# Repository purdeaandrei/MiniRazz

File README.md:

# MiniRazz - open hardware controller replacement for the Mini M keyboard.

This is a replacement keyboard controller, for the Unicomp Mini M
keyboard, this is an independent community project that is not endorsed by
Unicomp, and it is not related to any official controller sold by them.

Licensed under CERN-OHL-P v2 or later

## Images

## How to order from JLCPCB:
1. Go to http://jlcpcb.com , sign in to your account (create one if you don't have one)
2. Click Order Now, click Add gerber file
3. Upload the .zip file from the "order" subfolder.
4. Wait for the gerbers to be processed.
5. Check that it correctly detected 4-layerboard.
6. Select PCB Qty you wish to build
7. Specify Layer Sequence, click Yes, And select L1=F_Cu L2=In1_Cu L3=In2_Cu L4=B_Cu
8. Set "Remove Order Number" to "Specify a location"
9. Scroll down, turn on the "SMT Assembly" option, turn it on
10. Select "PCBA Type" = "Economic"
11. Select "Assembly Side" = "Top Side"
12. Select "Tooling holes" = "Added by Customer"
13. Click "I agree to the Terms and Conditions..."
14. Click "Next" on the right side
15. Click "Next" on the right side
16. Click "Add BOM File", upload the "*_bom_jlc.csv" file from the "order" subfolder.
17. Click "Add CPL File", upload the "*_cpl_jlc.csv" file from the "order" subfolder.
18. Click "Process BPM & CPL"
19. Take a look at what parts are available. At the time of writing J2/J3 triomate connectors were only available if pre-ordered (at a higher cost than ordering from DigiKey).
    You may be able to optimize cost by choosing to solder certain parts yourself, through-hole parts being the most likely candidate. (Please see the following section)
20. Click "Next", you will also have to click "Do Not Place" if some components are missing.
21. Check the rotation of components. JLCPCB may change default rotation in their component libraries at any time, and also position and rotation of the triomates has not been verified.
    - Check that component pins line up correctly with pads
    - Check that components which have polarity (usually marked with a dot) are oriented towards an assimetric marking on the silkscreen (for example for the memory and the io expander there's an extra line, while for the RP2040 there's a missing corner line to mark pin 1)
22. Click "Next"
23. Select Product Description: Office Appliance.../Keyboard...
24. Save to Cart, Check Out.

Cost analysis at the time of writing (2024 Aug 11):

| Qty | JLCPCB (USD) | JLC shipping est. (USD) | Digikey Triomates (USD) | Digikey shipping est. (USD) | VAT (19%) USD | Total (USD) | Coast per Board (USD) |
|-----|--------------|-------------------------|-------------------------|-----------------------------|---------------|-------------|-----------------------|
| 5   |   84.34      | 23.80                   | 14.66                   | 30                          | 29.03         | 181.83      | 36.37                 |
| 10  |  106.13      | 29.80                   | 29.32                   | 30                          | 37.10         | 232.35      | 23.24                 |
| 15  |  130.10      | 55.54                   | 43.76                   | 30                          | 49.29         | 308.69      | 20.58                 |
| 20  |  154.18      | 57.74                   | 58.35                   | 30                          | 57.05         | 357.32      | 17.87                 |

## Components of this design that may have to be ordered separately:
- 2 pcs of 16-pin 90-degree triomate connectors / board:
   - Part number: `6-520314-6` (TE Connectivity AMP Connectors)
   - [Digikey](https://www.digikey.com/en/products/detail/te-connectivity-amp-connectors/6-520314-6/1153749)
   - If the 90-degree connectors are not in stock, then you may also be able to get away with vertical ones (part number `6-520315-6`)
      - This has not yet been tested for fit in the keyboard.
   - JLCPCB now has it in its library, however it's not in stock.
     - You can pre-order it, and then have them assemble it, however it may not make financial sense (current costs are higher than from digikey, and you have to order 5 pcs extra for attrition.)
       - If you decide to have JLCPCB assemble this component, it is present in the bom/cpl files, but make sure the connector position/rotations are connect. I could not verify because they weren't in stock at the time I last checked.

## Other through hole components that may make sense to buy separately and to solder yourself:
- USB connector with locking tab
   - Part number: `LUSBA11100` (AMPHENOL COMMUNICATIONS SOLUTIONS)
   - [Digikey](https://www.digikey.com/en/products/detail/amphenol-cs-commercial-products/LUSBA11100/1956311?s=N4IgTCBcDaIDIFUDKAhAggRiwBmyAugL5A)
   - [Farnell](https://ro.farnell.com/amphenol-icc-commercial-products/lusba11100/usb-conn-2-0-type-a-receptacle/dp/2708971?CMP=e-email-sys-orderack-GLB)
- Optional 90 degree headers for solenoid support. You can use one of two options:
   - An 1x4 90-degree header: (recommended)
      - You will need to use single jumper wires to connect the solenoid driver, (or need to crimp a custom cable with dupont connectors)
   - A 2x3 90-degree header: (not recommended)
      - This may not fit well in the space available, and you may need to add tape to isolate the bottom of the backplate.

## Firmware

VIAL-QMK and ZMK firmwares are available, (plain QMK upstreaming will also be attempted).

### VIAL Firmware
Download from here:
https://github.com/purdeaandrei/vial-qmk-minirazz/releases

Use `unicomp_mini_m_minirazz_vial.uf2` or `unicomp_mini_m_minirazz_vial_debug.uf2`

### ZMK Firmware
The ZMK firmware can be downloaded by clicking Releases here: https://github.com/purdeaandrei/minirazz-zmk-config
The keymap can be customized by forking this repository, and editing the keymap. The firmware will be automatically rebuilt by github, and will be available on the "Actions" tab.
If you want to keep your keymap secret, you can copy the content of this repository into a private github repository.

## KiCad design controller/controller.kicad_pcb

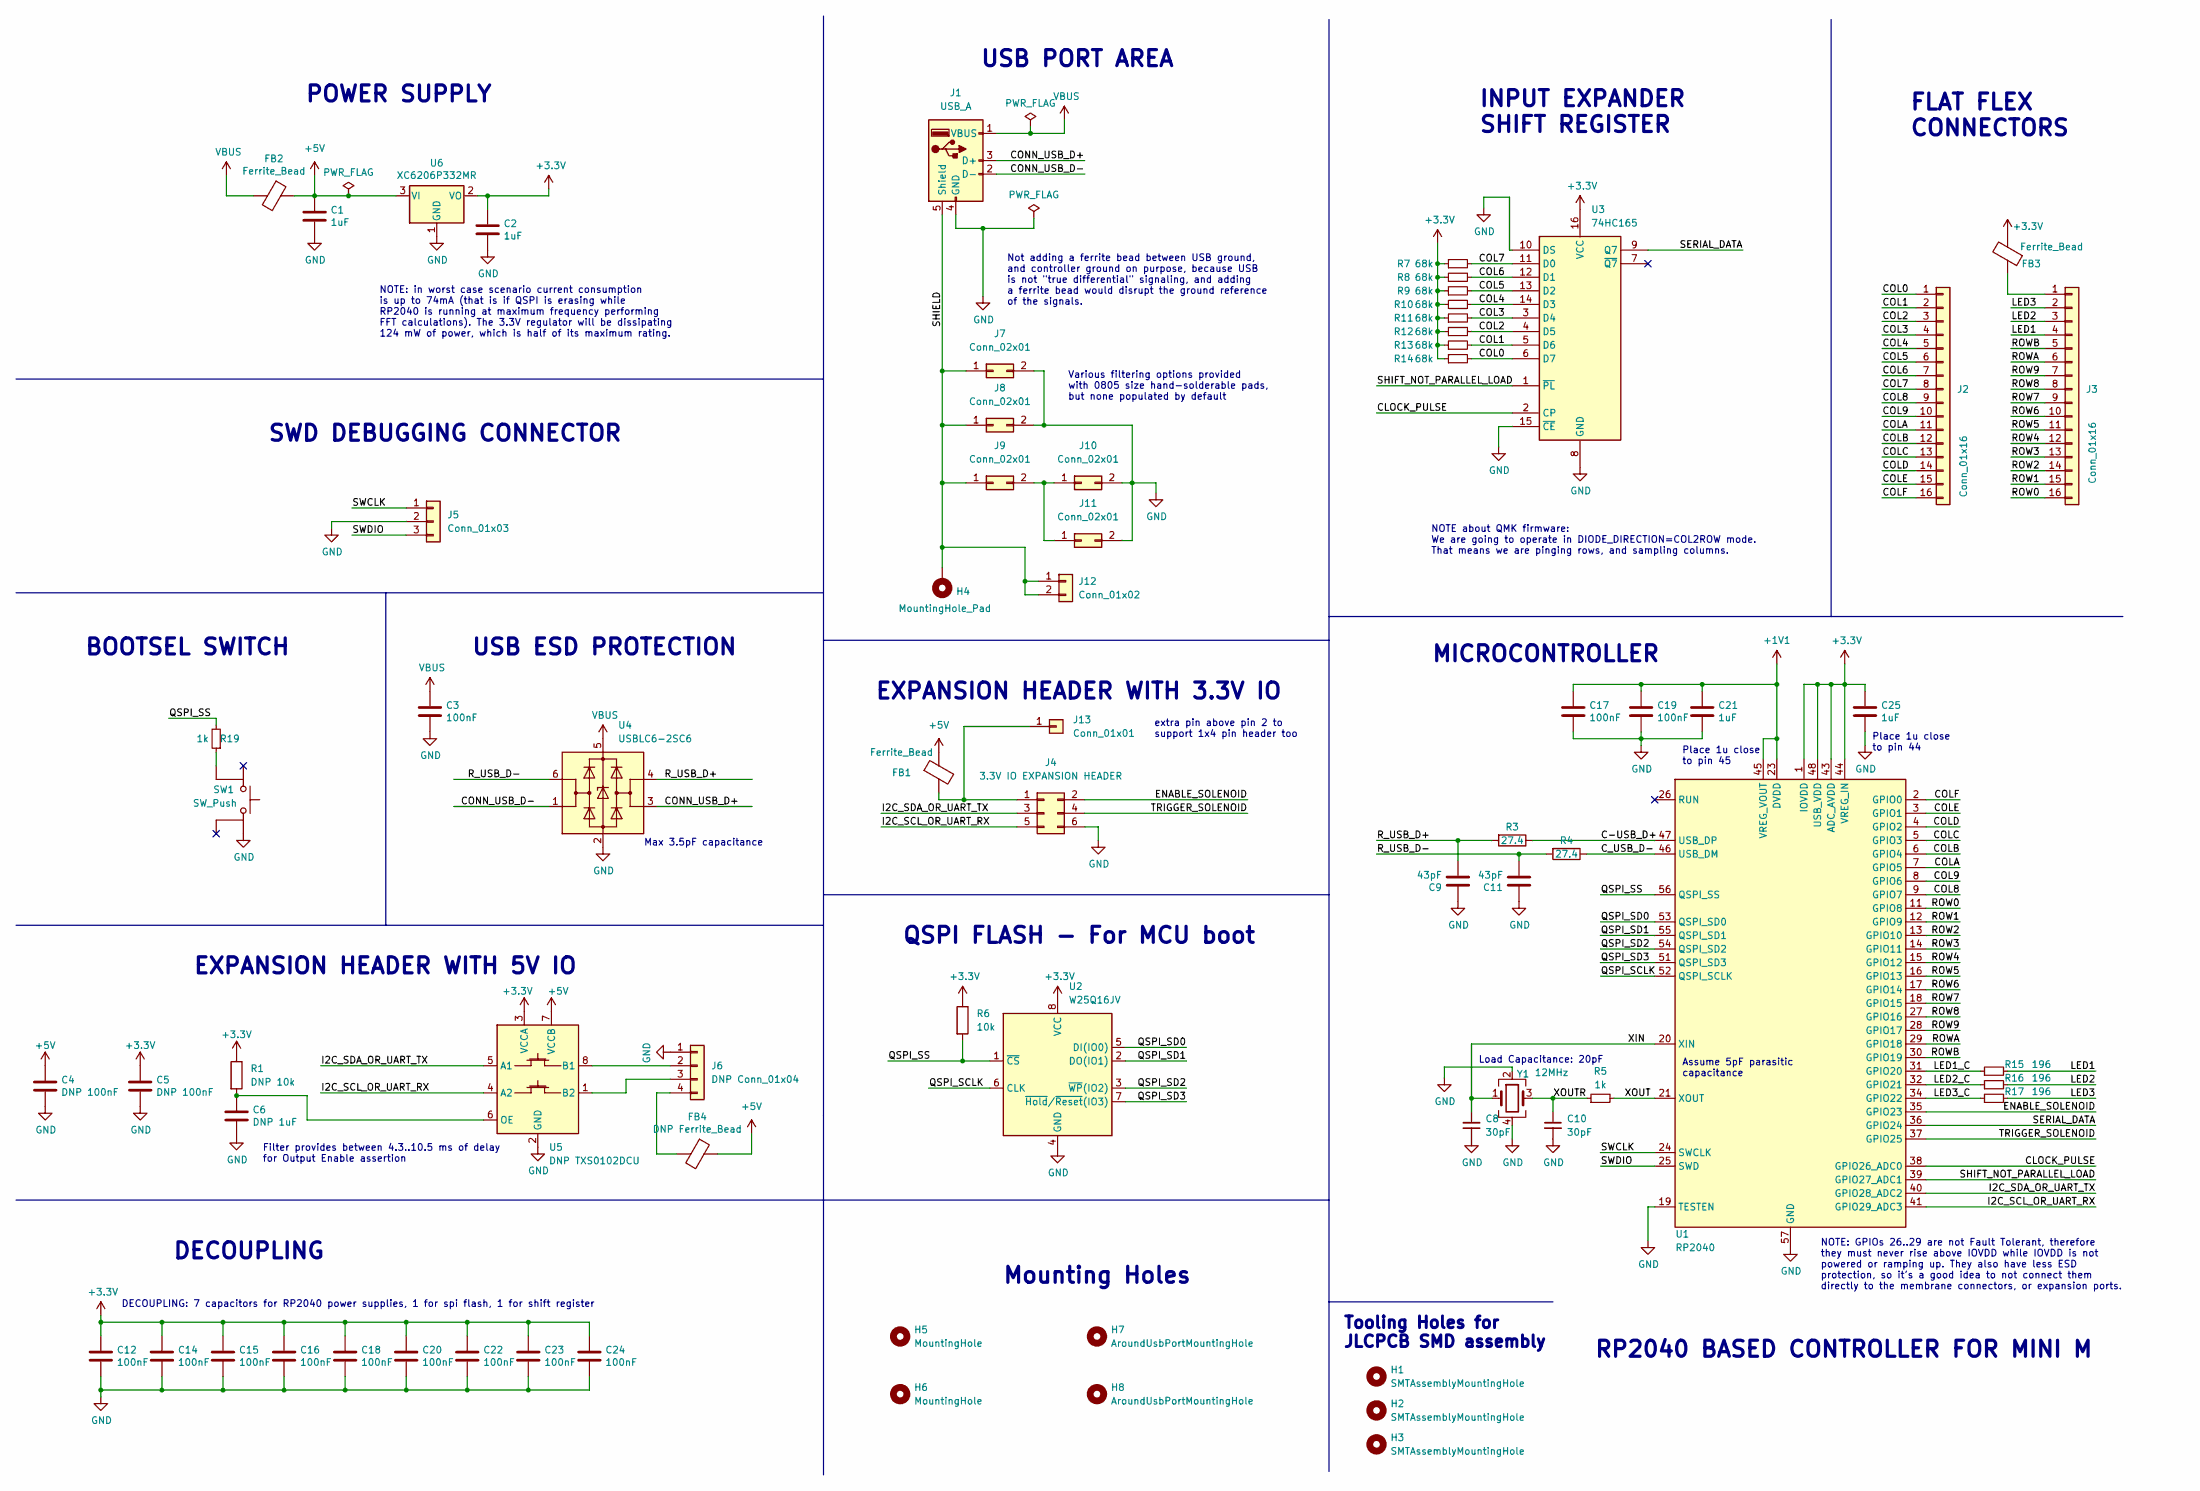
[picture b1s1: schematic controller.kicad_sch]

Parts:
C1, C2, C21, C25: 1uF; C_0402_1005Metric; LCSC C52923
C3, C12, C14, C15, C16, C17, C18, C19, C20, C22, C23, C24: 100nF; C_0402_1005Metric; LCSC C1525
C4, C5: DNP 100nF; C_0805_2012Metric_Pad1.18x1.45mm_HandSolder
C6: DNP 1uF; C_0805_2012Metric_Pad1.18x1.45mm_HandSolder
C8, C10: 30pF; C_0402_1005Metric; LCSC C1570
C9, C11: 43pF; C_0402_1005Metric; LCSC C415393
FB1, FB2, FB3: Ferrite_Bead; L_0805_2012Metric_Pad1.15x1.40mm_HandSolder; LCSC C1015
FB4: DNP Ferrite_Bead; L_0805_2012Metric_Pad1.15x1.40mm_HandSolder; LCSC C1015
H1, H2, H3: SMTAssemblyMountingHole; tooling_hole
H4: MountingHole_Pad; MountingHole_3mm_Pad
H5, H6: MountingHole; MountingHole_3mm
H7, H8: AroundUsbPortMountingHole; MountingHole_3.5mm
J1: USB_A; LUSB_A111_00
J2, J3: Conn_01x16; TE_connectivity_AMP_6-520314-6
J4: 3.3V IO EXPANSION HEADER; PinHeader_2x03_P2.54mm_Vertical_3dhorizontal
J5: Conn_01x03; PinHeader_1x03_P2.54mm_Vertical
J6: DNP Conn_01x04; JST_PH_S4B-PH-K_1x04_P2.00mm_Horizontal
J7, J8, J11: Conn_02x01; C_0805_2012Metric_Pad1.18x1.45mm_HandSolder
J9: Conn_02x01; R_0805_2012Metric_Pad1.20x1.40mm_HandSolder
J10: Conn_02x01; C_0402_1005Metric_Pad0.74x0.62mm_HandSolder
J12: Conn_01x02; JST_PH_B2B-PH-K_1x02_P2.00mm_Vertical
J13: Conn_01x01; PinHeader_1x01_P2.54mm_Vertical_3dhorizontal
R1: DNP 10k; R_0805_2012Metric_Pad1.20x1.40mm_HandSolder; LCSC C25744
R3, R4: 27.4; R_0402_1005Metric; LCSC C284479
R5, R19: 1k; R_0402_1005Metric; LCSC C11702
R6: 10k; R_0402_1005Metric; LCSC C25744
R7, R8, R9, R10, R11, R12, R13, R14: 68k; R_0402_1005Metric; LCSC C36871
R15, R16, R17: 196; R_0402_1005Metric; LCSC C270631
SW1: SW_Push; switch_K2-1187SQ-A4SW-06; LCSC C92584
U1: RP2040; QFN-56-1EP_7x7mm_P0.4mm_EP3.2x3.2mm; LCSC C2040
U2: W25Q16JV; SOIC-8_5.275x5.275mm_P1.27mm; LCSC C82317
U3: 74HC165; SOIC-16_3.9x9.9mm_P1.27mm; LCSC C5613
U4: USBLC6-2SC6; SOT-23-6; LCSC C2827654
U5: DNP TXS0102DCU; VSSOP-8_2.3x2mm_P0.5mm
U6: XC6206P332MR; SOT-23; LCSC C5446
Y1: 12MHz; Crystal_SMD_3225-4Pin_3.2x2.5mm_HandSoldering; LCSC C9002

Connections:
+1V1: C17.1, C19.1, C21.1, U1.23 (DVDD), U1.45 (VREG_VOUT), U1.50 (DVDD)
+3.3V: C2.1, C5.1, C12.1, C14.1, C15.1, C16.1, C18.1, C20.1, C22.1, C23.1, C24.1, C25.1, FB3.2, R1.1, R6.1, R7.1, R8.1, R9.1, R10.1, R11.1, R12.1, R13.1, R14.1, U1.1 (IOVDD), U1.10 (IOVDD), U1.22 (IOVDD), U1.33 (IOVDD), U1.42 (IOVDD), U1.43 (ADC_AVDD), U1.44 (VREG_IN), U1.48 (USB_VDD), U1.49 (IOVDD), U2.8 (VCC), U3.16 (VCC), U5.3 (VCCA), U6.2 (VO)
/C-USB_D+: R3.1, U1.47 (USB_DP)
/CLOCK_PULSE: U1.38 (GPIO26_ADC0), U3.2 (CP)
/COL0: J2.1, R14.2, U3.6 (D7)
/COL1: J2.2, R13.2, U3.5 (D6)
/COL2: J2.3, R12.2, U3.4 (D5)
/COL3: J2.4, R11.2, U3.3 (D4)
/COL4: J2.5, R10.2, U3.14 (D3)
/COL5: J2.6, R9.2, U3.13 (D2)
/COL6: J2.7, R8.2, U3.12 (D1)
/COL7: J2.8, R7.2, U3.11 (D0)
/COL8: J2.9, U1.9 (GPIO7)
/COL9: J2.10, U1.8 (GPIO6)
/COLA: J2.11, U1.7 (GPIO5)
/COLB: J2.12, U1.6 (GPIO4)
/COLC: J2.13, U1.5 (GPIO3)
/COLD: J2.14, U1.4 (GPIO2)
/COLE: J2.15, U1.3 (GPIO1)
/COLF: J2.16, U1.2 (GPIO0)
/CONN_USB_D+: J1.3 (D+), U4.3 (I/O2)
/CONN_USB_D-: J1.2 (D-), U4.1 (I/O1)
/C_USB_D-: R4.1, U1.46 (USB_DM)
/ENABLE_SOLENOID: J4.2, U1.35 (GPIO23)
/I2C_SCL_OR_UART_RX: J4.5, U1.41 (GPIO29_ADC3), U5.4 (A2)
/I2C_SDA_OR_UART_TX: J4.3, U1.40 (GPIO28_ADC2), U5.5 (A1)
/LED1: J3.4, R15.2
/LED1_C: R15.1, U1.31 (GPIO20)
/LED2: J3.3, R16.2
/LED2_C: R16.1, U1.32 (GPIO21)
/LED3: J3.2, R17.2
/LED3_C: R17.1, U1.34 (GPIO22)
/QSPI_SCLK: U1.52 (QSPI_SCLK), U2.6 (CLK)
/QSPI_SD0: U1.53 (QSPI_SD0), U2.5 (DI(IO0))
/QSPI_SD1: U1.55 (QSPI_SD1), U2.2 (DO(IO1))
/QSPI_SD2: U1.54 (QSPI_SD2), U2.3 (~WP(IO2))
/QSPI_SD3: U1.51 (QSPI_SD3), U2.7 (~Hold/~Reset(IO3))
/QSPI_SS: R6.2, R19.2, U1.56 (QSPI_SS), U2.1 (~CS)
/ROW0: J3.16, U1.11 (GPIO8)
/ROW1: J3.15, U1.12 (GPIO9)
/ROW2: J3.14, U1.13 (GPIO10)
/ROW3: J3.13, U1.14 (GPIO11)
/ROW4: J3.12, U1.15 (GPIO12)
/ROW5: J3.11, U1.16 (GPIO13)
/ROW6: J3.10, U1.17 (GPIO14)
/ROW7: J3.9, U1.18 (GPIO15)
/ROW8: J3.8, U1.27 (GPIO16)
/ROW9: J3.7, U1.28 (GPIO17)
/ROWA: J3.6, U1.29 (GPIO18)
/ROWB: J3.5, U1.30 (GPIO19)
/R_USB_D+: C9.2, R3.2, U4.4 (I/O2)
/R_USB_D-: C11.2, R4.2, U4.6 (I/O1)
/SERIAL_DATA: U1.36 (GPIO24), U3.9 (Q7)
/SHIELD: H4.1, J1.5 (Shield), J7.1, J8.1, J9.1, J12.1, J12.2
/SHIFT_NOT_PARALLEL_LOAD: U1.39 (GPIO27_ADC1), U3.1 (~PL)
/SWCLK: J5.1, U1.24 (SWCLK)
/SWDIO: J5.3, U1.25 (SWD)
/TRIGGER_SOLENOID: J4.4, U1.37 (GPIO25)
/XIN: C8.1, U1.20 (XIN), Y1.1
/XOUT: R5.2, U1.21 (XOUT)
/XOUTR: C10.1, R5.1, Y1.3
unnamed: C6.1, R1.2, U5.6 (OE)
unnamed: FB1.2, J4.1, J13.1
unnamed: FB3.1, J3.1
unnamed: FB4.2, J6.4
unnamed: J6.2, U5.8 (B1)
unnamed: J6.3, U5.1 (B2)
unnamed: J9.2, J10.1, J11.1
unnamed: R19.1, SW1.2

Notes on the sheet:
DECOUPLING: 7 capacitors for RP2040 power supplies, 1 for spi flash, 1 for shift register
USB PORT AREA
Tooling Holes for JLCPCB SMD assembly
Place 1u close to pin 45
Max 3.5pF capacitance
Place 1u close to pin 44
FLAT FLEX CONNECTORS
Not adding a ferrite bead between USB ground, and controller ground on purpose, because USB is not "true differential" signaling, and adding a ferrite bead would disrupt the ground reference of the signals.
Various filtering options provided with 0805 size hand-solderable pads, but none populated by default
EXPANSION HEADER WITH 5V IO
NOTE: GPIOs 26..29 are not Fault Tolerant, therefore they must never rise above IOVDD while IOVDD is not powered or ramping up. They also have less ESD protection, so it's a good idea to not connect them directly to the membrane connectors, or expansion ports.
Load Capacitance: 20pF
USB ESD PROTECTION
QSPI FLASH - For MCU boot
RP2040 BASED CONTROLLER FOR MINI M
extra pin above pin 2 to support 1x4 pin header too
Mounting Holes
BOOTSEL SWITCH
DECOUPLING
EXPANSION HEADER WITH 3.3V IO
NOTE: in worst case scenario current consumption is up to 74mA (that is if QSPI is erasing while RP2040 is running at maximum frequency performing FFT calculations). The 3.3V regulator will be dissipating 124 mW of power, which is half of its maximum rating.
Filter provides between 4.3..10.5 ms of delay for Output Enable assertion
POWER SUPPLY
MICROCONTROLLER
NOTE about QMK firmware: We are going to operate in DIODE_DIRECTION=COL2ROW mode. That means we are pinging rows, and sampling columns.
SWD DEBUGGING CONNECTOR
INPUT EXPANDER SHIFT REGISTER
Assume 5pF parasitic capacitance

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
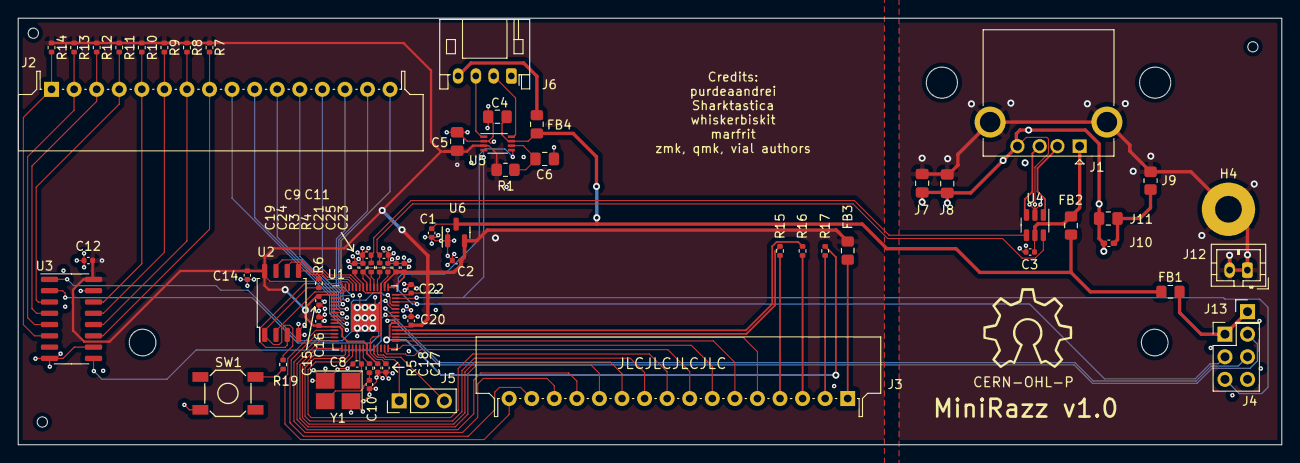
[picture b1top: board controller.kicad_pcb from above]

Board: 4 copper layers, 142.2 x 48.0 mm, 73 parts (0 on the bottom side), 72 nets.

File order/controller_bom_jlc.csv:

"Comment","Designator","Footprint","LCSC Part #"
"1uF","C1,C2,C21,C25","C_0402_1005Metric","C52923"
"100nF","C3,C12,C14,C15,C16,C17,C18,C19,C20,C22,C23,C24","C_0402_1005Metric","C1525"
"30pF","C8,C10","C_0402_1005Metric","C1570"
"43pF","C9,C11","C_0402_1005Metric","C415393"
"Ferrite_Bead","FB1,FB2,FB3","L_0805_2012Metric_Pad1.15x1.40mm_HandSolder","C1015"
"27.4","R3,R4","R_0402_1005Metric","C284479"
"1k","R5,R19","R_0402_1005Metric","C11702"
"10k","R6","R_0402_1005Metric","C25744"
"68k","R7,R8,R9,R10,R11,R12,R13,R14","R_0402_1005Metric","C36871"
"196","R15,R16,R17","R_0402_1005Metric","C270631"
"SW_Push","SW1","switch_K2-1187SQ-A4SW-06","C92584"
"RP2040","U1","QFN-56-1EP_7x7mm_P0.4mm_EP3.2x3.2mm","C2040"
"W25Q16JV","U2","SOIC-8_5.275x5.275mm_P1.27mm","C82317"
"74HC165","U3","SOIC-16_3.9x9.9mm_P1.27mm","C5613"
"USBLC6-2SC6","U4","SOT-23-6","C2827654"
"XC6206P332MR","U6","SOT-23","C5446"
"12MHz","Y1","Crystal_SMD_3225-4Pin_3.2x2.5mm_HandSoldering","C9002"

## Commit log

2023-02-13 added digikey link to usb connector
2023-03-12 Firmware readme updated
2024-08-11 Added LCSC part numbers for through-hole components
2024-08-11 small fix to README
